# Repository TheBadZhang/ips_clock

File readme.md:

# IPS_CLOCK

基于 合宙ESP32C3+LuatOS+Bootstrap 开发设计的物联网时钟

其实还有nat内网穿透

实现了点击按钮执行操作，并将操作结果同步到网页中
同时实现了打开网页自动同步当前状态

暂时就这样了，以后有啥东西以后再加

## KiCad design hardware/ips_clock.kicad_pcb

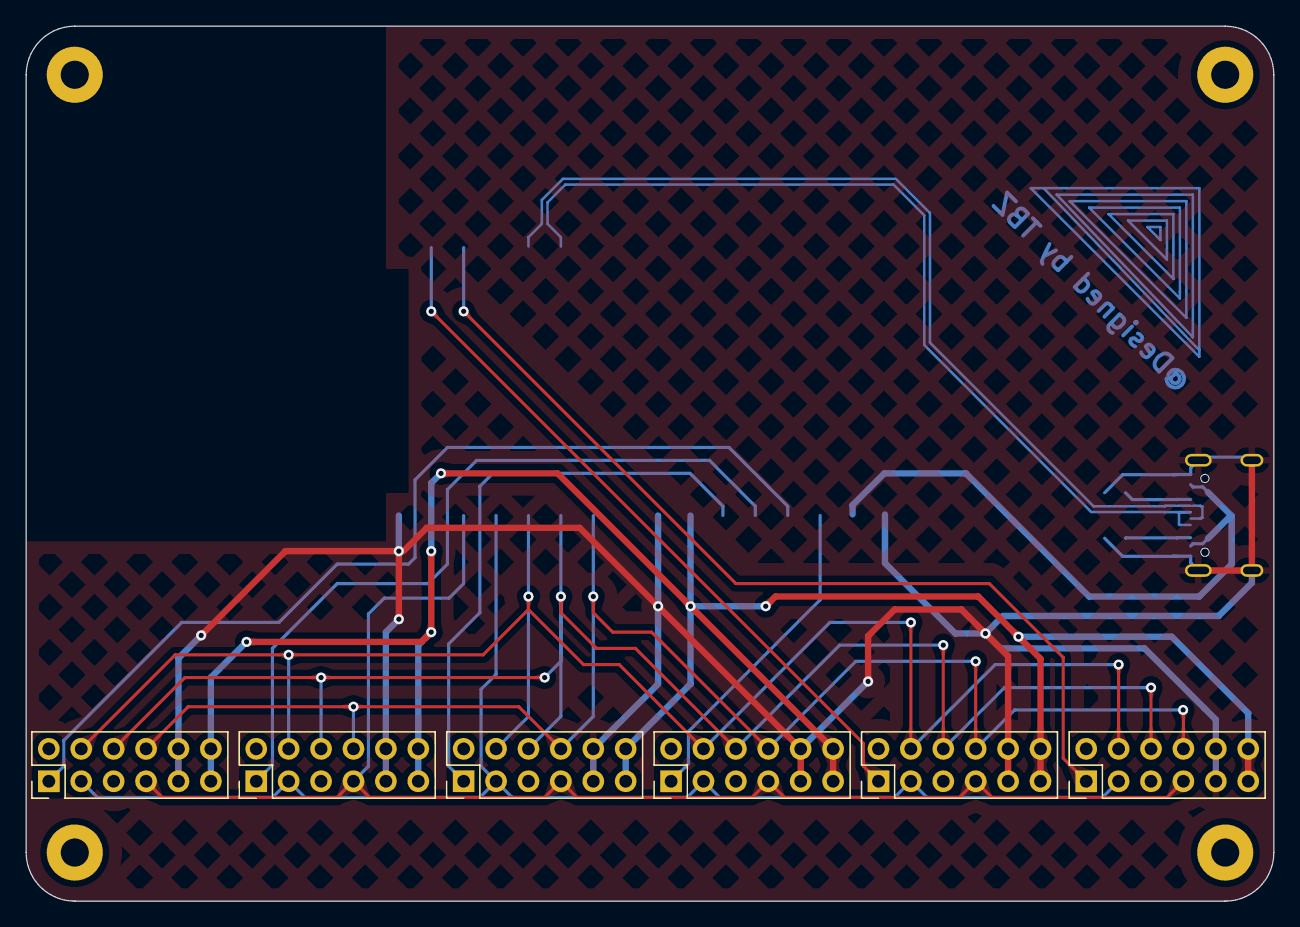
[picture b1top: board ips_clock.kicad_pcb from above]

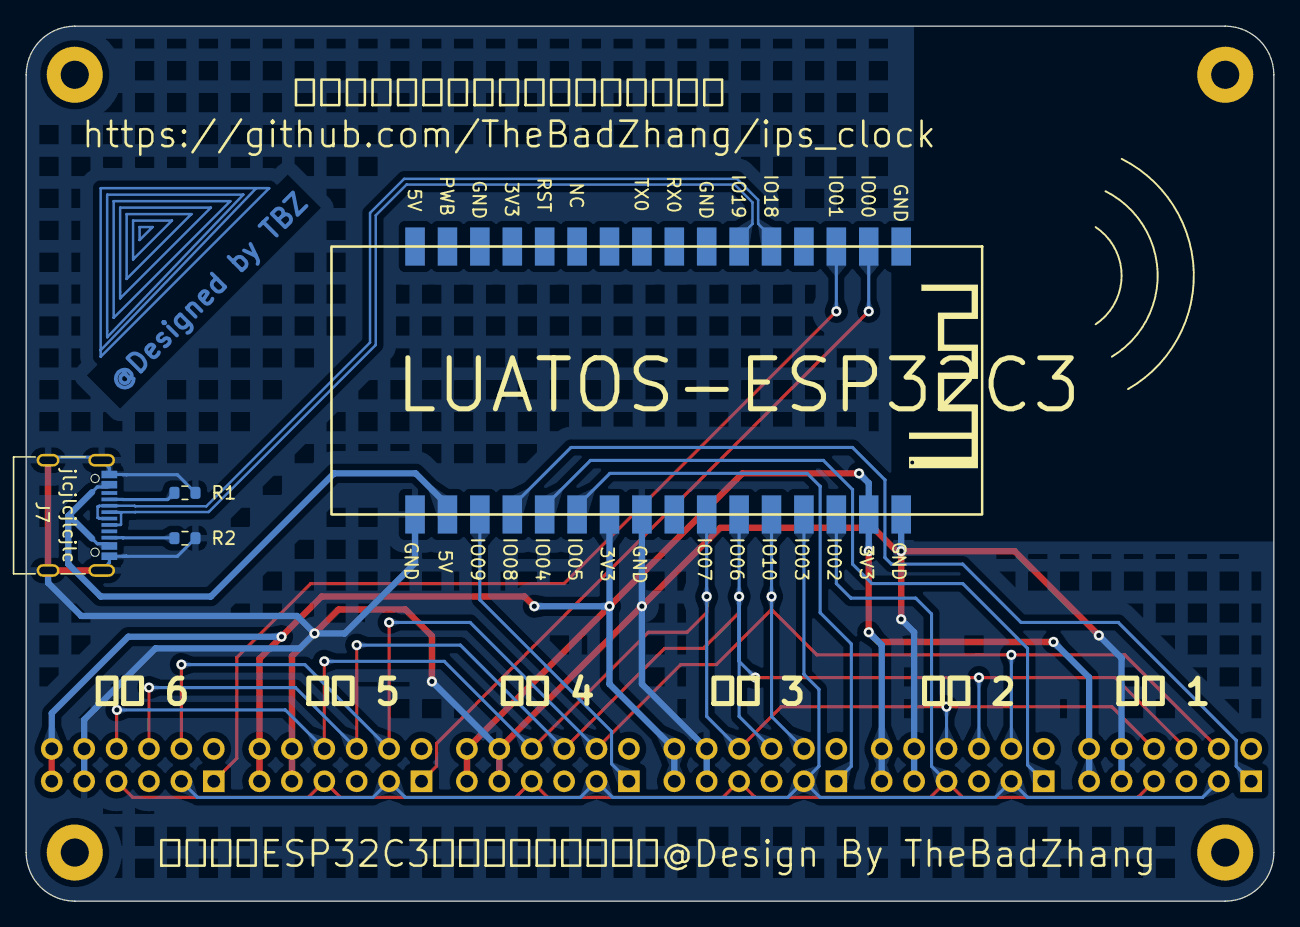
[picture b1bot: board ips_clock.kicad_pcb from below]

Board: 2 copper layers, 97.8 x 68.6 mm, 14 parts (4 on the bottom side), 18 nets.

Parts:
H1, H2, H3, H4: MountingHole; MountingHole_2.2mm_M2_Pad
J1, J2, J3, J4, J5, J6: Conn_02x06_Top_Bottom; PMOD-HOST
J7: USB_C_Receptacle_USB2.0; USB_C_Receptacle_G-Switch_GT-USB-7010ASV
R1, R2: 5.1K; R_0603_1608Metric
U1: LUAT-ESP32-C3

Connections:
+3V3: J1.6, J1.12, J2.6, J2.12, J3.6, J3.12, J4.6, J4.12, J5.6, J5.12, J6.6, J6.12, U1.18 (3.3V), U1.26 (3.3V)
+5V: J7.A4 (VBUS), J7.A9 (VBUS), J7.B4 (VBUS), J7.B9 (VBUS), U1.31 (5V)
/BLK: J1.10, J2.10, J3.10, J4.10, J5.10, J6.10, U1.23 (SPI_CS/GPIO07)
/CS1: J1.1, U1.29 (GPIO08)
/CS2: J2.1, U1.28 (ADC4/I2C_SDA/GPIO04)
/CS3: J3.1, U1.27 (I2C_SCL/GPIO05)
/CS4: J4.1, U1.30 (GPIO09/BOOT)
/CS5: J5.1, U1.2 (GPIO00/UART1_TX/ADC0)
/CS6: J6.1, U1.3 (GPIO01/UART1_RX/ADC1)
/DC: J1.9, J2.9, J3.9, J4.9, J5.9, J6.9, U1.22 (GPIO06)
/RST: J1.8, J2.8, J3.8, J4.8, J5.8, J6.8, U1.21 (SPI_MISO/GPIO10)
/SCL: J1.4, J2.4, J3.4, J4.4, J5.4, J6.4, U1.19 (ADC2/SPI_CLK/GPIO02)
/SDA: J1.2, J2.2, J3.2, J4.2, J5.2, J6.2, U1.20 (ADC3/SPI_MOSI/GPIO03)
/UD+: J7.A6 (D+), J7.B6 (D+), U1.6 (GPIO19/USB_D+)
/UD-: J7.A7 (D-), J7.B7 (D-), U1.5 (GPIO18/USB_D-)
GND: J1.5, J1.11, J2.5, J2.11, J3.5, J3.11, J4.5, J4.11, J5.5, J5.11, J6.5, J6.11, J7.A1 (GND), J7.A12 (GND), J7.B1 (GND), J7.B12 (GND), J7.S1 (SHIELD), R1.2, R2.2, U1.17 (GND), U1.25 (GND), U1.32 (GND)
unnamed: J7.A5 (CC1), R1.1
unnamed: J7.B5 (CC2), R2.1

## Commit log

2023-06-18 初始化提交
2023-06-18 添加了说明文档
2023-06-18 移动图片的路径使项目更整洁
2023-06-18 移动图片路径
2023-06-18 合并软硬件项目
2023-06-18 添加硬件设计文件到项目中
2023-06-18 删除了多余的注释
2023-06-18 修改灯状态的初始样式
2023-06-18 分离html、js、css
2023-06-28 最后更新了PCB的布局
2023-07-03 修改了原来测试用的代码，适配最新的板子
2023-07-03 删除了错误的，固件中未包含的库
2023-07-24 修改因为硬件产生的bug
    因为屏幕没有按照最新的设计进行生产，新屏幕模块的引脚定义与原先不同，导致原先代码失效，飞线后得以正常工作
2023-07-24 更新了PCB上esp32c3的模型为官方开源的模型，先前未开源
2023-07-24 导出了原理图，方便之后在线查看
2023-07-24 删除了碍眼的res文件夹
